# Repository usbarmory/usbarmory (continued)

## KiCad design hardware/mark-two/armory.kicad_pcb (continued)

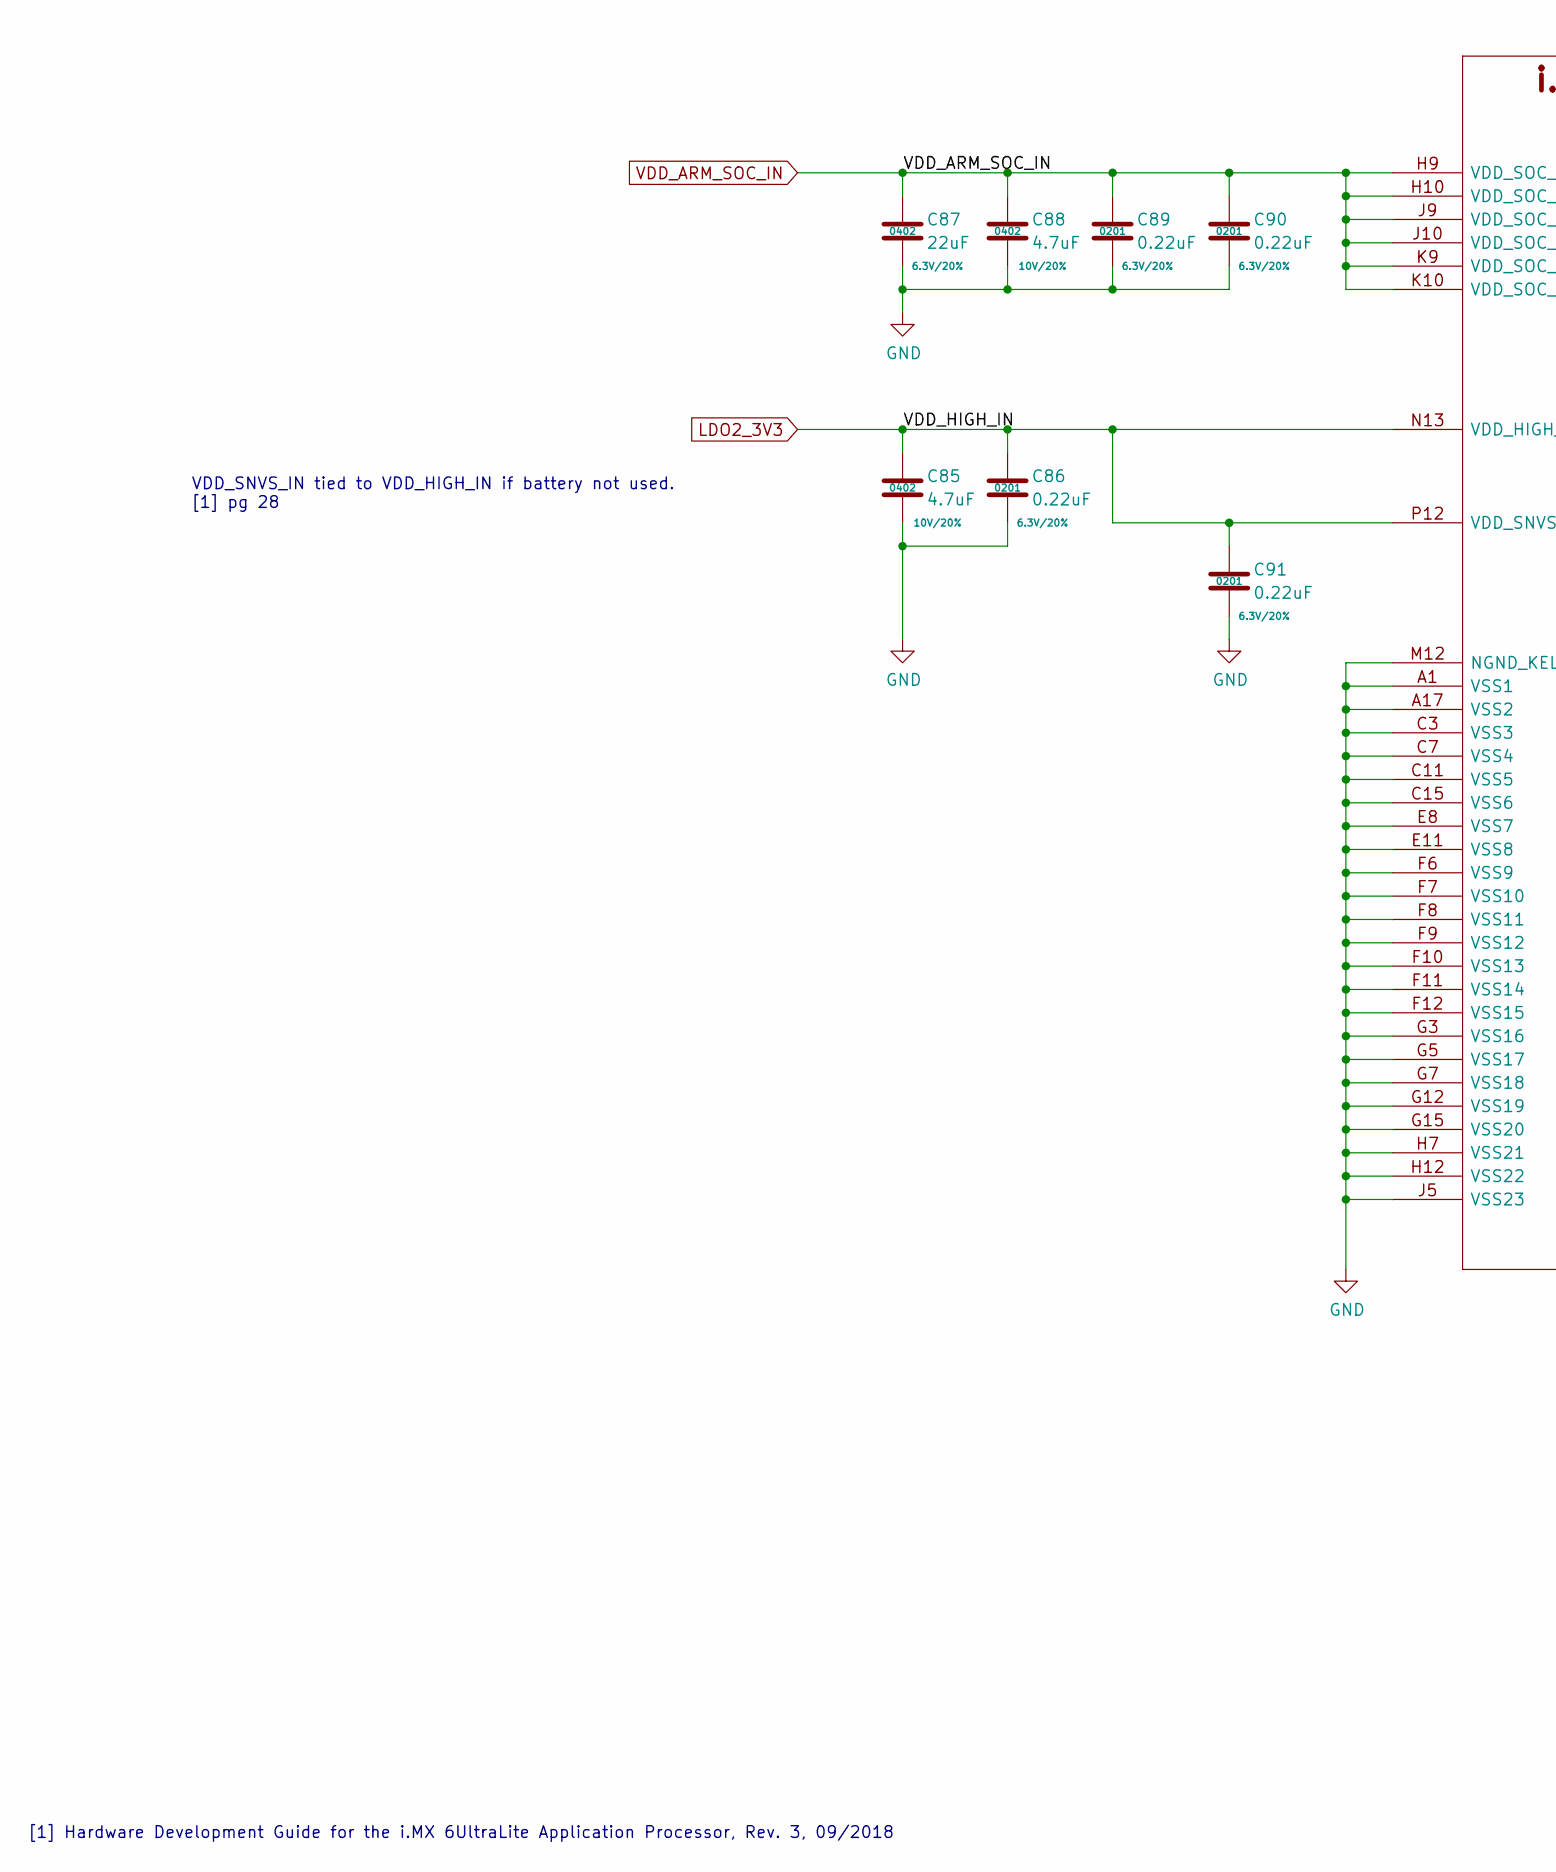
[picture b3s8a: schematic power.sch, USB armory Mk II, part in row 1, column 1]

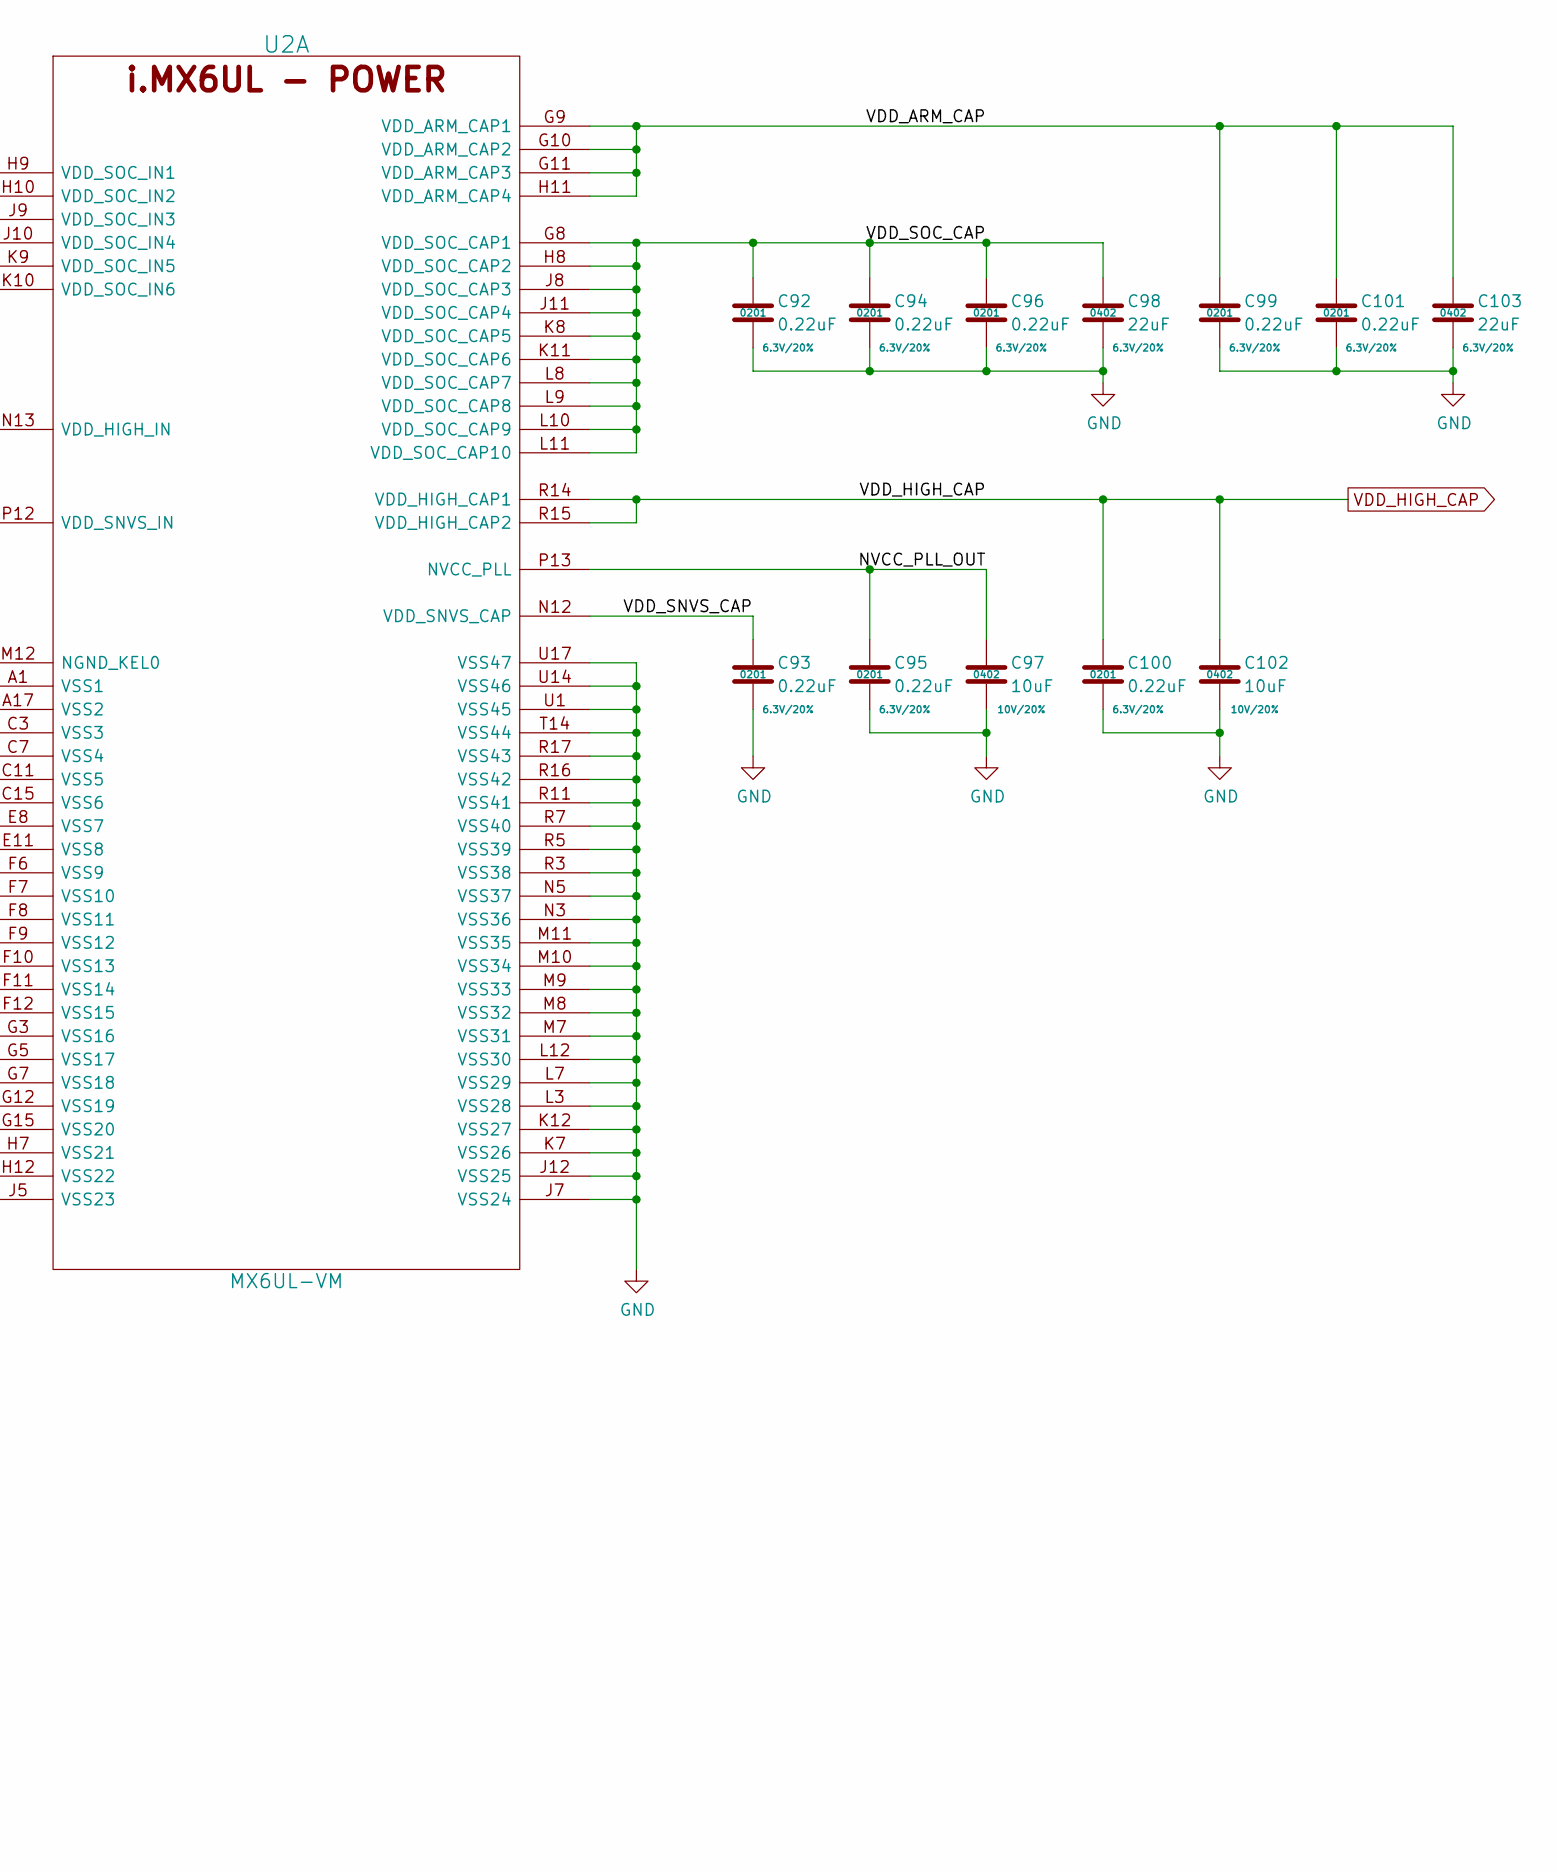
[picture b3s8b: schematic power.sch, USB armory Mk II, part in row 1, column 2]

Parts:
C85, C88: 4.7uF; SM0402; Rating 10V/20%; Mfg PN ZRB15XR61A475ME01D
C86, C89, C90, C91, C92, C93, C94, C95, C96, C99, C100, C101: 0.22uF; SM0201; Rating 6.3V/20%; Mfg PN GRM033R60J224ME15D
C87, C98, C103: 22uF; SM0402; Rating 6.3V/20%; Mfg PN CL05A226MQ5N6J8
C97, C102: 10uF; SM0402; Rating 10V/20%; Mfg PN CL05A106MP8NUB8
U2: MX6UL-VM; SOT1534-2; Mfg PN MCIMX6Z0DVM09AB

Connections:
/Power/NVCC_PLL_OUT: C95.1, C97.1, U2.P13 (NVCC_PLL)
/Power/VDD_ARM_CAP: C99.1, C101.1, C103.1, U2.G9 (VDD_ARM_CAP1), U2.G10 (VDD_ARM_CAP2), U2.G11 (VDD_ARM_CAP3), U2.H11 (VDD_ARM_CAP4)
/Power/VDD_SNVS_CAP: C93.1, U2.N12 (VDD_SNVS_CAP)
/Power/VDD_SOC_CAP: C92.1, C94.1, C96.1, C98.1, U2.G8 (VDD_SOC_CAP1), U2.H8 (VDD_SOC_CAP2), U2.J8 (VDD_SOC_CAP3), U2.J11 (VDD_SOC_CAP4), U2.K8 (VDD_SOC_CAP5), U2.K11 (VDD_SOC_CAP6), U2.L8 (VDD_SOC_CAP7), U2.L9 (VDD_SOC_CAP8), U2.L10 (VDD_SOC_CAP9), U2.L11 (VDD_SOC_CAP10)
GND: C85.2, C86.2, C87.2, C88.2, C89.2, C90.2, C91.2, C92.2, C93.2, C94.2, C95.2, C96.2, C97.2, C98.2, C99.2, C100.2, C101.2, C102.2, C103.2, U2.A1 (VSS1), U2.A17 (VSS2), U2.C3 (VSS3), U2.C7 (VSS4), U2.C11 (VSS5), U2.C15 (VSS6), U2.E8 (VSS7), U2.E11 (VSS8), U2.F6 (VSS9), U2.F7 (VSS10), U2.F8 (VSS11), U2.F9 (VSS12), U2.F10 (VSS13), U2.F11 (VSS14), U2.F12 (VSS15), U2.G3 (VSS16), U2.G5 (VSS17), U2.G7 (VSS18), U2.G12 (VSS19), U2.G15 (VSS20), U2.H7 (VSS21), U2.H12 (VSS22), U2.J5 (VSS23), U2.J7 (VSS24), U2.J12 (VSS25), U2.K7 (VSS26), U2.K12 (VSS27), U2.L3 (VSS28), U2.L7 (VSS29), U2.L12 (VSS30), U2.M7 (VSS31), U2.M8 (VSS32), U2.M9 (VSS33), U2.M10 (VSS34), U2.M11 (VSS35), U2.M12 (NGND_KEL0), U2.N3 (VSS36), U2.N5 (VSS37), U2.R3 (VSS38), U2.R5 (VSS39), U2.R7 (VSS40), U2.R11 (VSS41), U2.R16 (VSS42), U2.R17 (VSS43), U2.T14 (VSS44), U2.U1 (VSS45), U2.U14 (VSS46), U2.U17 (VSS47); also elsewhere on the board
LDO2_3V3: C85.1, C86.1, C91.1, U2.N13 (VDD_HIGH_IN), U2.P12 (VDD_SNVS_IN); also elsewhere on the board
VDD_ARM_SOC_IN: C87.1, C88.1, C89.1, C90.1, U2.H9 (VDD_SOC_IN1), U2.H10 (VDD_SOC_IN2), U2.J9 (VDD_SOC_IN3), U2.J10 (VDD_SOC_IN4), U2.K9 (VDD_SOC_IN5), U2.K10 (VDD_SOC_IN6); also elsewhere on the board
VDD_HIGH_CAP: C100.1, C102.1, U2.R14 (VDD_HIGH_CAP1), U2.R15 (VDD_HIGH_CAP2); also elsewhere on the board

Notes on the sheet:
[1] Hardware Development Guide for the i.MX 6UltraLite Application Processor, Rev. 3, 09/2018
VDD_SNVS_IN tied to VDD_HIGH_IN if battery not used. [1] pg 28

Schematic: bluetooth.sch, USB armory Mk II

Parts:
C104: 0.1uF; SM0201; Rating 10V/20%; Mfg PN GRM033R61A104ME15D
TP8, TP9: TestPoint; TP
U11: ANNA-B112; Mfg PN ANNA-B112-01B

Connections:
/Bluetooth/ANT_INT: U11.5 (ANT_INT), U11.6 (ANT)
/Bluetooth/ANT_PCB: U11.1 (ANT_PCB)
BT_RESET_B: U11.12 (~RESET); also elsewhere on the board
BT_SWDCLK: U11.39 (SWD_CLK); also elsewhere on the board
BT_SWDIO: U11.40 (SWD_IO); also elsewhere on the board
BT_SWITCH_1: U11.30 (GREEN/SWITCH_1); also elsewhere on the board
BT_SWITCH_2: U11.38 (SWITCH_2); also elsewhere on the board
BT_UART_CTS: U11.35 (UART_CTS); also elsewhere on the board
BT_UART_DSR: U11.26 (UART_DSR); also elsewhere on the board
BT_UART_DTR: U11.25 (UART_DTR); also elsewhere on the board
BT_UART_RTS: U11.34 (UART_RTS); also elsewhere on the board
BT_UART_RX: TP9.1, U11.19 (UART_TXD); also elsewhere on the board
BT_UART_TX: TP8.1, U11.20 (UART_RXD); also elsewhere on the board
DCDC_3V3: C104.1, U11.9 (VCC); also elsewhere on the board
GND: C104.2, U11.4 (GND), U11.7 (GND), U11.8 (GND), U11.10 (GND), U11.11 (GND), U11.17 (XL1), U11.18 (XL2), U11.32 (GND), U11.33 (GND), U11.41 (GND), U11.42 (GND), U11.43 (GND), U11.44 (GND), U11.46 (GND), U11.47 (GND), U11.48 (GND), U11.49 (GND), U11.50 (GND), U11.51 (GND), U11.52 (GND); also elsewhere on the board

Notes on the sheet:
When using internal oscillator XL1 and XL2 should be connected to ground ([1] pg 11).
Use internal antenna.
[1] ANNA-B112 - System Integration Manual (UBX-18009821-R07)
There is no strict requirement of adding bypass capacitance to the supply net close to the module. But depending on the layout of the supply net and other consumers on the same net, bypass capacitors might still be beneficial. [1] pg 40
NFC_1 and NFC_2: floating Not found any reference, but should be safe as they are also GPIO.
Integrated antenna module placed - in the corner of the PCB: ANT_PCB -> GND pattern ANT_GND_x -> NC - on the side of the PCB: ANT_PCB -> NC ANT_GND_x -> GND [1] pg 14
RESET_N: 13 kOhm internal pull-up. [2] pg 28
[2] ANNA-B112 - Data Sheet (UBX-18011707-R04)
It has been witnessed that the ANNA-B112 can be back-powered via UART pins. To turn completelly off the module all the interfaces pins should be kept low.

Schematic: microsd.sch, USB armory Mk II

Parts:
C37: 0.22uF; SM0201; Rating 6.3V/20%; Mfg PN GRM033R60J224ME15D
C105: 10uF; SM0402; Rating 10V/20%; Mfg PN CL05A106MP8NUB8
C106: 0.1uF; SM0201; Rating 10V/20%; Mfg PN GRM033R61A104ME15D
J1: microSD slot; MOLEX_503182-1852; Mfg PN 503182-1852
R54: 22R; SM0201; Rating 50mW/1%; Mfg PN CRCW020122R0JNED
R55, R56: 10K; SM0201; Rating 50mW/1%; Mfg PN CRCW020110K0JNED
U2: MX6UL-VM; SOT1534-2; Mfg PN MCIMX6Z0DVM09AB
U12: PUSB3TB6; SOT1358-1; Mfg PN PUSB3TB6AZ
U20, U21: TPD1E10B06; X1SON-2; Mfg PN TPD1E10B06DPYR

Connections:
/microSD/SD1_CLK: J1.5 (CLK), R54.1, U12.2 (CH2)
/microSD/SD1_CLK_R: R54.2, U2.C1 (SD1_CLK)
/microSD/SD1_CMD: J1.3 (CMD), R55.2, U2.C2 (SD1_CMD), U12.6 (CH5)
/microSD/SD1_DATA0: J1.7 (DAT0), R56.2, U2.B3 (SD1_DATA0), U12.7 (CH6)
/microSD/SD1_DATA1: J1.8 (DAT1), U2.B2 (SD1_DATA1), U12.1 (CH1)
/microSD/SD1_DATA2: J1.1 (DATA2), U2.B1 (SD1_DATA2), U12.5 (CH4)
/microSD/SD1_DATA3: J1.2 (CD/DAT3), U2.A2 (SD1_DATA3), U12.3 (CH3)
DCDC_3V3: C105.1, C106.1, J1.4 (VDD), U21.1; also elsewhere on the board
GND: C37.2, C105.2, C106.2, J1.6 (VSS), J1.DT (DETECT), J1.P1 (SHIELD), J1.P2 (SHIELD), J1.P3 (SHIELD), J1.P4 (SHIELD), J1.P5 (SHIELD), U12.4 (GND), U20.2, U21.2; also elsewhere on the board
SD1_CD_B: J1.SW (SWITCH), U20.1; also elsewhere on the board
SD_3V3_1V8: C37.1, R55.1, R56.1, U2.C4 (NVCC_SD1); also elsewhere on the board

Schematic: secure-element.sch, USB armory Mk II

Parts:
C5, C107: 0.1uF; SM0201; Rating 10V/20%; Mfg PN GRM033R61A104ME15D
R29: 10K; SM0201; Rating 50mW/1%; Mfg PN CRCW020110K0JNED
U4: SE050; SOT1969-1; Mfg PN SE050C1HQ1/Z01SCZ
U13: ATECC608B-DNP; UDFN-8; Mfg PN ATECC608B-MAHDA

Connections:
DCDC_3V3: C5.1, C107.1, R29.1, U4.12 (VIN), U13.8 (VCC); also elsewhere on the board
GND: C5.2, C107.2, U4.1 (ISO_14443_LB), U4.14 (ISO_7816_RST_N), U4.17 (ISO_14443_LA), U4.19 (VSS), U4.21 (Thermal), U13.4 (GND), U13.T (THERMAL); also elsewhere on the board
I2C1_SCL: U4.10 (I2C_SCL), U13.6 (SCL); also elsewhere on the board
I2C1_SDA: U4.9 (I2C_SDA), U13.5 (SDA); also elsewhere on the board
unnamed: U4.15 (VOUT), U4.18 (VCC)
SE050_ENA: R29.2, U4.11 (ENA); also elsewhere on the board

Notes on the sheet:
Optional, not mounted on retail units.

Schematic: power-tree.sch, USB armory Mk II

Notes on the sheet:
USB1_VBUS
USB2_VBUS
USB_VBUS
i.MX6ULZ
NVCC_ENET
VDD_SOC_IN
VDD_HIGH_IN
VDD_SNVS_IN
USB_OTG1_VBUS
VDDA_ADC_3P3
NVCC_GPIO
NVCC_CSI
NVCC_NAND
NVCC_SD1
NVCC_LCD
NVCC_UART
USB_OTG2_VBUS
NVCC_DRAM
NVCC_DRAM_2P5
Type-C port controller
VIN
FUSB303 - RCPT
TUSB320 - PLUG
Bluetooth module
u-blox ANNA-B112
Type-C debug switch
FSA1208
push-push slot
microSD
4GB/8GB/16GB eMMC
eMMC
DDR3L 512 MB / 1 GB
DDR
Microchip ATECC608A
Secure Element 1
Logic inverter
SN74LVC1G04
Type-C power switch
NX5P3090
A10

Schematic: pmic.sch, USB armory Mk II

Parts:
C1, C2, C3, C23: 4.7uF; SM0402; Rating 10V/20%; Mfg PN ZRB15XR61A475ME01D
C4, C8, C9, C10, C14, C15, C25: 1uF; SM0201; Rating 10V/20%; Mfg PN GRM033R61A105ME15D
C11, C12: 0.1uF; SM0201; Rating 10V/20%; Mfg PN GRM033R61A104ME15D
C13: 2.2uF; SM0402; Rating 25V/20%; Mfg PN GRM155R61E225ME15D
C16: 47uF; SM0603; Rating 6.3V/20%; Mfg PN GRM188R60J476ME15D
C17, C18, C20, C21, C22, C24, C26, C32: 10uF; SM0402; Rating 10V/20%; Mfg PN CL05A106MP8NUB8
C27: 0.47uF; SM0201; Rating 6.3V/20%; Mfg PN GRM033R60J474ME90D
L1, L2, L3: 1uH; SM0603; Rating 1.7A/20%/128mOhm; Mfg PN DFE18SAN1R0MG0L
R1, R2, R22: 100K; SM0201; Rating 50mW/1%; Mfg PN CRCW0201100KJNED
U1: MC34PF1510A6EP; SOT1369-4; Mfg PN MC34PF1510A6EP

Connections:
/PMIC/LICELL: C12.1, U1.31 (LICELL)
/PMIC/VCORE: C14.1, U1.24 (VCORE)
/PMIC/VDIG: C15.1, U1.23 (VDIG)
/PMIC/VSNVS_3V: C27.1, R1.1, R22.1, U1.30 (VSNVS)
/PMIC/VSYS: C1.1, C2.1, C3.1, C4.1, C8.1, C9.1, C16.1, R2.1, U1.11 (VLDO3IN), U1.14 (SW3IN), U1.17 (SW2IN), U1.20 (VLDO2IN), U1.26 (SW1IN), U1.28 (VLDO1IN), U1.35 (VSYS1), U1.36 (VSYS2)
DCDC_3V3: C11.1, C24.1, C26.1, L3.2, U1.4 (VDDIO), U1.15 (SW3FB); also elsewhere on the board
DDR_1V35: C10.1, C20.1, C22.1, L2.2, U1.16 (SW2FB), U1.22 (VINREFDDR); also elsewhere on the board
DDR_VREF: C25.1, U1.21 (VREFDDR); also elsewhere on the board
EMMC_1V8: C32.1, U1.29 (VLDO1); also elsewhere on the board
GND: C1.2, C2.2, C3.2, C4.2, C8.2, C9.2, C10.2, C11.2, C12.2, C13.2, C14.2, C15.2, C16.2, C17.2, C18.2, C20.2, C21.2, C22.2, C23.2, C24.2, C25.2, C26.2, C27.2, C32.2, U1.5 (VDDOTP), U1.7 (STANDBY), U1.32 (GND), U1.40 (GND), U1.41 (EP); also elsewhere on the board
I2C1_SCL: U1.3 (SCL); also elsewhere on the board
I2C1_SDA: U1.2 (SDA); also elsewhere on the board
LDO2_3V3: C21.1, U1.19 (VLDO2); also elsewhere on the board
unnamed: L1.1, U1.25 (SW1LX)
unnamed: L2.1, U1.18 (SW2LX)
unnamed: L3.1, U1.13 (SW3LX)
unnamed: R1.2, U1.6 (PWRON)
unnamed: R2.2, U1.8 (ONKEY)
PMIC_WDI: R22.2, U1.1 (WDI); also elsewhere on the board
SD_3V3_1V8: C23.1, U1.12 (VLDO3); also elsewhere on the board
VDD_ARM_SOC_IN: C17.1, C18.1, L1.2, U1.27 (SW1FB); also elsewhere on the board
VSYS_5V: C13.1, U1.37 (VIN); also elsewhere on the board

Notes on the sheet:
[1] PF1510 - Power management integrated circuit (PMIC) for low power application processors Rev 1.0, 23 May 2018
EPAD: Tie to the inner and external ground planes through vias to allow effective thermal dissipation. [1] pg 8
400 mA
300 mA
1 A
10 mA
Power rails
ULL/ULZ: NXP MC34PF1510A6EP UL: NXP MC32PF1510A3EP

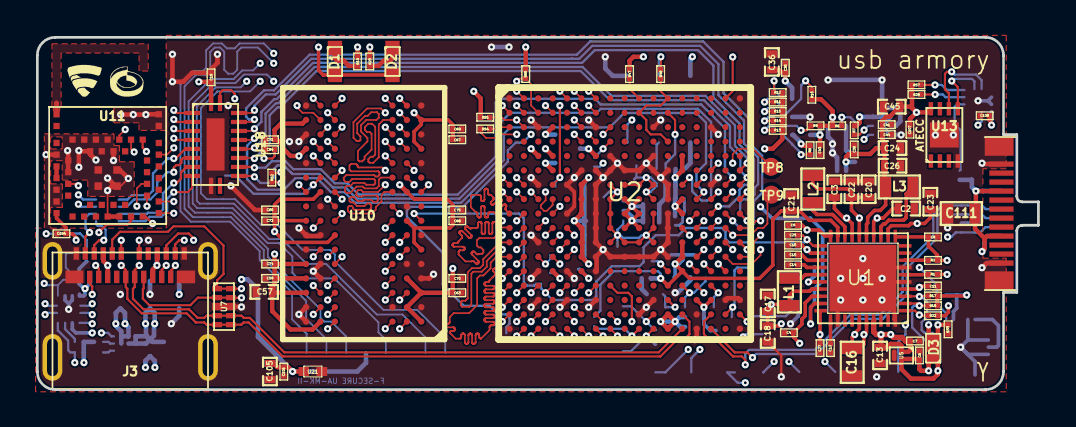
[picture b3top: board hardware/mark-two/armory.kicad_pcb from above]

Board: 6 copper layers, 55.6 x 19.6 mm, 195 parts (0 on the bottom side), 172 nets.

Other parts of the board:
FSC_LOGO_NO_TEXT_SMALL: G***; FSC_LOGO_NO_TEXT_SMALL
FSC_LOGO_NO_TEXT_SMALL#2: G***; FSC_LOGO_NO_TEXT_SMALL
Ref**: Val**; IP_LOGO_NO_TEXT_SMALL
Ref**#2: Val**; IP_LOGO_NO_TEXT_SMALL

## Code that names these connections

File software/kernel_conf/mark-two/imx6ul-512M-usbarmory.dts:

/*
 * USB armory Mk II device tree file
 * https://github.com/inversepath/usbarmory
 *
 * Copyright (c) The USB armory authors
 * Andrej Rosano <andrej@inversepath.com>
 *
 * This file is dual-licensed: you can use it either under the terms
 * of the GPL or the X11 license, at your option. Note that this dual
 * licensing only applies to this file, and not this project as a
 * whole.
 *
 *  a) This file is free software; you can redistribute it and/or
 *     modify it under the terms of the GNU General Public License as
 *     published by the Free Software Foundation; either version 2 of the
 *     License, or (at your option) any later version.
 *
 *     This file is distributed in the hope that it will be useful,
 *     but WITHOUT ANY WARRANTY; without even the implied warranty of
 *     MERCHANTABILITY or FITNESS FOR A PARTICULAR PURPOSE.  See the
 *     GNU General Public License for more details.
 *
 * Or, alternatively,
 *
 *  b) Permission is hereby granted, free of charge, to any person
 *     obtaining a copy of this software and associated documentation
 *     files (the "Software"), to deal in the Software without
 *     restriction, including without limitation the rights to use,
 *     copy, modify, merge, publish, distribute, sublicense, and/or
 *     sell copies of the Software, and to permit persons to whom the
 *     Software is furnished to do so, subject to the following
 *     conditions:
 *
 *     The above copyright notice and this permission notice shall be
 *     included in all copies or substantial portions of the Software.
 *
 *     THE SOFTWARE IS PROVIDED "AS IS", WITHOUT WARRANTY OF ANY KIND,
 *     EXPRESS OR IMPLIED, INCLUDING BUT NOT LIMITED TO THE WARRANTIES
 *     OF MERCHANTABILITY, FITNESS FOR A PARTICULAR PURPOSE AND
 *     NONINFRINGEMENT. IN NO EVENT SHALL THE AUTHORS OR COPYRIGHT
 *     HOLDERS BE LIABLE FOR ANY CLAIM, DAMAGES OR OTHER LIABILITY,
 *     WHETHER IN AN ACTION OF CONTRACT, TORT OR OTHERWISE, ARISING
 *     FROM, OUT OF OR IN CONNECTION WITH THE SOFTWARE OR THE USE OR
 *     OTHER DEALINGS IN THE SOFTWARE.
 */

/dts-v1/;

#include "imx6ul.dtsi"

/ {
	model = "F-Secure USB armory Mk II";
	compatible = "inversepath,imx6ul-usbarmory-mkII", "fsl,imx6ul";

	chosen {
		stdout-path = &uart2;
	};

	memory {
		device_type = "memory";
		reg = <0x80000000 0x20000000>;
	};

	leds {
		compatible = "gpio-leds";
		pinctrl-names = "default";
		pinctrl-0 = <&pinctrl_led>;

		led-white {
			label = "LED_WHITE";
			gpios = <&gpio4 21 GPIO_ACTIVE_LOW>;
			linux,default-trigger = "heartbeat";
		};

		led-blue {
			label = "LED_BLUE";
			gpios = <&gpio4 22 GPIO_ACTIVE_LOW>;
		};
	};

	regulators {
		compatible = "simple-bus";
		#address-cells = <1>;
		#size-cells = <0>;

		reg_sd1_vmmc: sd1_regulator {
			compatible = "regulator-fixed";
			regulator-name = "VSD_3V3";
			regulator-min-microvolt = <3300000>;
			regulator-max-microvolt = <3300000>;
		};
	};
};

&uart1 {
	pinctrl-names = "default";
	pinctrl-0 = <&pinctrl_bluetooth>;
	uart-has-rtscts;
	status = "okay";
};

&uart2 {
	pinctrl-names = "default";
	pinctrl-0 = <&pinctrl_uart2>;
	status = "okay";
};

&usdhc1 {
	pinctrl-names = "default";
	pinctrl-0 = <&pinctrl_usdhc1>;
	no-1-8-v;
	keep-power-in-suspend;
	wakeup-source;
	status = "okay";
};

&usdhc2 {
	pinctrl-names = "default";
	pinctrl-0 = <&pinctrl_usdhc2>;
	non-removable;
	status = "okay";
};

&i2c1 {
	pinctrl-0 = <&pinctrl_i2c1>;
	status = "okay";
};

&iomuxc {
	pinctrl_uart2: uart2grp {
		fsl,pins = <
			MX6UL_PAD_UART2_TX_DATA__UART2_DCE_TX	0x1b0b1
			MX6UL_PAD_UART2_RX_DATA__UART2_DCE_RX	0x1b0b1
		>;
	};

	pinctrl_bluetooth: uart1grp {
		fsl,pins = <
			MX6UL_PAD_UART1_TX_DATA__UART1_DCE_TX	0x1b0b0 /* BT_UART_TX  */
			MX6UL_PAD_UART1_RX_DATA__UART1_DCE_RX	0x1b0b0 /* BT_UART_RX  */
			MX6UL_PAD_UART1_CTS_B__UART1_DCE_CTS	0x1b0b0 /* BT_UART_CTS */
			MX6UL_PAD_GPIO1_IO07__UART1_DCE_RTS	0x130b0 /* BT_UART_RTS */
			MX6UL_PAD_UART3_TX_DATA__GPIO1_IO24	0x1f020 /* BT_UART_DSR */
			MX6UL_PAD_UART3_RX_DATA__GPIO1_IO25	0x10020 /* BT_UART_DTR */
			MX6UL_PAD_GPIO1_IO04__GPIO1_IO04	0x1f020 /* BT_SWDCLK   */
			MX6UL_PAD_GPIO1_IO06__GPIO1_IO06	0x1f020 /* BT_SWDIO    */
			MX6UL_PAD_GPIO1_IO09__GPIO1_IO09	0x1f020 /* BT_RESET    */
			MX6UL_PAD_UART3_RTS_B__GPIO1_IO27	0x1f020 /* BT_SWITCH_1 */
			MX6UL_PAD_UART3_CTS_B__GPIO1_IO26	0x1f020 /* BT_SWITCH_2 */
		>;
	};

	pinctrl_i2c1: i2c1grp {
		fsl,pins = <
			MX6UL_PAD_GPIO1_IO02__I2C1_SCL	0x4001b8b0
			MX6UL_PAD_GPIO1_IO03__I2C1_SDA	0x4001b8b0
		>;
	};

	pinctrl_led: ledgrp {
		fsl,pins = <
			MX6UL_PAD_CSI_DATA00__GPIO4_IO21	0x1f020
			MX6UL_PAD_CSI_DATA01__GPIO4_IO22	0x1f020
		>;
	};

	pinctrl_usdhc1: usdhc1grp {
		fsl,pins = <
			MX6UL_PAD_SD1_CMD__USDHC1_CMD		0x1f019
			MX6UL_PAD_SD1_CLK__USDHC1_CLK		0x1f019
			MX6UL_PAD_SD1_DATA0__USDHC1_DATA0	0x1f019
			MX6UL_PAD_SD1_DATA1__USDHC1_DATA1	0x1f019
			MX6UL_PAD_SD1_DATA2__USDHC1_DATA2	0x1f019
			MX6UL_PAD_SD1_DATA3__USDHC1_DATA3	0x1f019
		>;
	};

	pinctrl_usdhc2: usdhc2grp {
		fsl,pins = <
			MX6UL_PAD_NAND_RE_B__USDHC2_CLK		0x10071
			MX6UL_PAD_NAND_WE_B__USDHC2_CMD		0x17059
			MX6UL_PAD_NAND_DATA00__USDHC2_DATA0	0x17059
			MX6UL_PAD_NAND_DATA01__USDHC2_DATA1	0x17059
			MX6UL_PAD_NAND_DATA02__USDHC2_DATA2	0x17059
			MX6UL_PAD_NAND_DATA03__USDHC2_DATA3	0x17059
			MX6UL_PAD_NAND_DATA04__USDHC2_DATA4	0x17059
			MX6UL_PAD_NAND_DATA05__USDHC2_DATA5	0x17059
			MX6UL_PAD_NAND_DATA06__USDHC2_DATA6	0x17059
			MX6UL_PAD_NAND_DATA07__USDHC2_DATA7	0x17059
		>;
	};
};

/ {
	soc {
		caam_sm: caam-sm@00100000 {
			 compatible = "fsl,imx7d-caam-sm", "fsl,imx6q-caam-sm";
			 reg = <0x00100000 0x3fff>;
		};

		irq_sec_vio: caam_secvio {
			     compatible = "fsl,imx7d-caam-secvio", "fsl,imx6q-caam-secvio";
			     interrupts = <GIC_SPI 20 IRQ_TYPE_LEVEL_HIGH>;
		};
	};

	caam_keyblob: caam-keyblob {
		compatible = "fsl,sec-v4.0-keyblob";
		status = "okay";
	};
};

&usbotg1 {
	dr_mode = "peripheral";
	disable-over-current;
	tpl-support;
	status = "okay";
};

&usbotg2 {
	dr_mode = "host";
	disable-over-current;
	tpl-support;
	status = "okay";
};

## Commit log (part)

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2016-06-08 Remove old U-Boot patches
2016-06-09 bump buildroot INTERLOCK revision
2016-06-20 Add patch for disabling U-Boot CLI
2016-06-21 devicetree: explicitly set IOMUX values
    Do not relay on bootloader values (e.g. using 0x80000000 settings).
2016-06-21 devicetree: remove vpu node
    VPU is already enabled in imx53.dtsi.
2016-06-23 out of an abundance of caution (as at that time haveged already took care of the pool) ensure that there is enough entropy for luksFormat command
2016-06-28 Update kernel config
    Add stack protector and DMA contiguous access support.
2016-06-29 add SCCv2 device
2016-07-01 add mxc-scc2 driver in buildroot image and fix invalid date reset format
2016-07-03 tidying
2016-07-27 Update kernel config
    Use regular stack protection as gcc included in some main Linux
    distributions does not support -fstack-protector-strong flag yet.
2016-08-31 Add config for Linux 4.7
2016-09-16 isolate networking and INTERLOCK overlays for better modularity and bump revisions
2016-09-19 buildroot overlays/profiles re-org
2016-10-12 csftool: add support for Serial download mode when using DCD
    When DCD is used, Serial downloader will move DCD into ocram and clear
    the DCD pointer in IVT - before signature verification.
    To sign the image properly we need to:
    - clear the DCD pointer in IVT and calculate signature on this modified image
    - make a signature for DCD copy in ocram (usually from 0x910000)
2016-10-12 typo fix
2016-10-12 disable NTP server to favor manual configuration by user
2016-10-12 set static CDC Ethernet MAC address
2016-10-12 buildroot fixes: ensure LED is turned on last at shutdown, tidy overlay structure
2016-10-14 Add config for Linux 4.8
2016-10-21 bugfixes for qubes-gpg-split/gpg-server execution
2016-10-31 bump buildroot INTERLOCK and kernel revision
2016-11-08 improve readibility
2016-11-08 Fix typo
2016-11-09 check for dropbearkey dependency and note it in documentation
2016-11-10 fail on any post build error
2016-11-14 style consistency fixes
2016-11-15 lock alias now actually locks the partition
2016-11-15 add missing sudo
2016-11-16 bump kernel
2016-11-16 set default LED timeout if not specified
2016-11-17 Updated kernel configuration.
    Add support for EXT4 extended attributes to allow setcap, enable /proc/config.gz by default.
2016-11-22 replace diagram
2016-12-13 Clean old kernel configs
2016-12-13 Update devicetree files
    Add dts files for kernel 4.9. Move old dts files to dts-4.8 directory.
2016-12-15 restore scc2 dts entry in separate file
2017-01-14 PaX/Grsecurity 4.8 for USBArmory
2017-01-14 More exploit mitigation on Linux v4.9
2017-02-15 PaX/Grsecurity 4.9 for USBArmory:
    PaX/Grsecurity 4.9 with BBR enabled for the case of tor-router usage.
2017-02-15 PaX/Grsecurity 4.9 for USBArmory: (#38)
    PaX/Grsecurity 4.9 with BBR enabled for the case of tor-router usage.
2017-03-07 bump buildroot, INTERLOCK and mxc-scc2 revisions
2017-03-15 cryptsetup aes-xts-plain64 is broken under 4.10 kernel when sahara is enabled, make it a module for blacklisting when required
2017-05-24 bump buildroot and kernel revision
2017-06-05 add preliminary HAB security advisory
2017-07-19 CVE-2017-7932 PoC and advisory update
2017-07-27 added link to i.MX Community post that lists affected P/Ns
2017-08-07 bump INTERLOCK version
2017-11-17 update kernel conf
2018-01-08 update buildroot environment
2018-01-09 adjust mkfs.ext4 path due to change in newer buildroot
2018-01-15 Enable kernel namespaces
2018-02-13 Fix ext2load dependancy in secure boot patches
2018-02-14 bump initial system date
2018-02-15 Enable hab_status in secure boot patches
2018-02-20 Add linux kernel 4.14 config
2018-02-26 Fix disable CLI patch
    2018.01 U-Boot requires CONFIG_USE_BOOTARGS
2018-02-28 bump buildroot kernel, U-Boot and INTERLOCK versions
2018-05-08 Fix ext2load command not available error
2018-07-10 copyright change
2018-10-18 tidying
    Remove configurations for unmantained kernel versions
2018-11-01 Add devicetree with CAAM for i.MX6UL PICO board
2018-11-01 Add buildroot caam-keyblob package
2018-11-01 Bump U-Boot in INTERLOCK buildroot for i.MX6UL PICO
2018-11-01 Tyding
2018-11-01 Add i.MX6UL PICO secure boot support
2018-11-02 U-Boot security advisory (CVE-2018-18440, CVE-2018-18439)
2018-11-02 Remove unnecessary U-Boot environment variables
2018-11-02 imx6ul-pico: add patch for disabling U-Boot CLI
2018-11-27 adjust buildroot profiles to use intree dts
2018-12-04 fix documentation - dtb destination file
2018-12-18 bump caam-keyblob version
2019-02-01 maintain original dtb name to respect usbarmory.its path
2019-02-01 Update buildroot release and kernel version
2019-03-19 Fix i2c, spi and gpio devicetree
    iomux pinctrl configuration should be placed in module structure instead
    of the 'iomux' one. This behaviour seems to have changed in recent
    kernels.
2019-03-20 Fix I2C, GPIO and SPI devicetree files
    Remove container node from iomuxc nodes.
2019-03-28 bump buildroot and kernel versions for INTERLOCK profile
2019-04-01 move mark-one specific design files in own directory
2019-04-03 Set SION bit for i2c pads
2019-04-10 i.MX6UL* bootrom dump utility
2019-05-06 Update 4.14 kernel config
2019-05-06 enable local system does not support BPF/cgroup based firewalling
2019-05-08 adjust links
2019-05-08 add image links
2019-06-05 USB armory Mk II alpha buildroot profile
2019-06-06 adjust LED path
2019-06-06 Update usbarmory mark-two devicetree
    Add support for bluetooth GPIOs (switches, reset, etc.)
2019-06-06 Fix DDR calibration values
2019-06-07 Add FUSB303 reset in U-Boot
2019-06-10 Disable over current detection for i.MX6UL
2019-06-10 i.MX6UL and i.MX6ULL device tree files update
    - enable hardware flow control on bluetooth uart
    - set plug USB port to peripheral mode
    - tidying
2019-06-12 preliminary mark-two 4.19 kernel configuration
2019-06-12 move mark-two buildroot configuration to kernel 4.19
2019-06-12 remove imx6ul pico configuration and replace it with mark-two specific one
2019-06-14 set i.MX6ULL as default DTS
2019-06-14 USB armory mark-two debug accessory
2019-06-20 comment FUSB303 i2c enable lines in u-boot patches
2019-06-20 adjust path
2019-06-20 use capabilities over tmpfs
2019-06-20 remove development ssh access
2019-06-21 enable CONFIG_IMX2_WDT to allow reboot
2019-06-24 force HAB_ENG_SW due to i.MX6ULL/i.MX6ULZ ERR010449
2019-06-27 Do not reloacate fdt initrd images
    Required to boot Linux on boards with 1GB RAM.
2019-06-27 Add U-Boot patches for boards with 1GB RAM
2019-07-01 disable CAAM on i.MX6ULL/i.MX6ULZ
2019-07-01 restore ENABLE on receptacle port
2019-07-01 bump kernel version
2019-07-01 restore USB PHY settings
2019-07-10 Fix U-Boot environment offset
    Move environment offset to 1MB to keep enough space for
    U-Boot image.
2019-07-12 first attempt at Travis CI for buildroot environment
2019-07-12 set variables as global
2019-07-12 reduce log size
2019-07-12 wait for make command
2019-07-12 remove travis integration due to time limit
2019-07-15 Add U-Boot 2017.04 patch for upstream
2019-07-22 set uSD as non-removable to work around U-Boot issue with CD
2019-07-22 specify i.MX6ULZ specific behaviour
2019-07-23 bump buildroot kernel versions
2019-07-23 Fix patch for upstream to support disabled console
    A revert of commit 80a48dd47e3bf3ede676fae5a630cb6c80de3e69
    is required to make the build successful, otherwise the following
    error is returned at the final linking stage:
    ...
    LDS u-boot.lds
    LD u-boot
2019-07-25 U-Boot advisory update
2019-07-31 bump buildroot kernel versions and apply updated mark-two u-boot patches
2019-07-31 Fix U-boot patch
    Add missing spaces in defconfig file.
2019-08-02 Fix IOMUX configuration for UART1 in U-Boot patch
2019-08-05 Fix U-Boot patch related to 1GB DDR support
2019-08-07 bump kernel versions
2019-08-07 Fix typos
2019-08-21 note orientation requirement
2019-08-26 clarify licensing
2019-09-09 Set dr_mode for plug port to peripheral
2019-09-25 Fix U-Boot mmc initialization
    Move iomux initialization for eMMC and microSD back to
    board file as the initialization via dts file appears buggy.
2019-09-30 bumped latest mxc-scc2 changeset
2019-11-07 USB armory Mk II project files + tidying
2019-11-08 add USB armory Mk II information in HAB advisory
2020-01-13 rename organization
2020-02-24 point to github page
2020-03-06 highlight default credentials
2020-03-18 add config for linux 5.4
2020-03-18 u-boot: specify boot configuration
    Mitigates CVE-2020-10648
    https://labs.f-secure.com/advisories/das-u-boot-verified-boot-bypass
2020-03-25 Fix argc argument to include USBARMORY_FIT_SIZE
    The argc argument in do_ext2load function is incorrect,
    preventing the use of USBARMORY_FIT_SIZE parameter.
2020-03-26 add serial console example for base Debian image
2020-04-02 Limit distro_bootcmd to scan a single boot device
    Regardless of the boot device, the distro_bootcmd scans both,
    microSD and eMMC, for boot scripts presence.
    A situation can arise where the U-Boot is booted from one device,
    and the Linux boot scripts are read from the other, preventing
    a complete boot from the expected device.
2020-04-02 Remove not required device tree blocks
2020-04-10 Add Mk II JTAG schematics
2020-04-24 Add DCD file for i.MX6ULZ 512MB
2020-05-04 Fix cpufreq support for imx6ulz
    https://groups.google.com/forum/#!topic/usbarmory/p4I0e22rKYw
2020-05-18 Updated DTS to use operating-points-v2 for imx6ulz
2020-06-03 remove U-Boot UMS patches, now replaced by armory-ums
2020-06-11 replace U-Boot UMS with armory-ums in buildroot installation procedure
2020-06-11 usbarmory linux: add CONFIG_SECURITY_APPARMOR
2020-06-12 u-boot: bump patches to 2020.04
2020-06-15 Fix verification boot for U-Boot 2020.04
    Remove the 'signature' devicetree block form imx6ul-usbarmory.dts
    as it goes in conflict with the one specified in usbarmory.its.
2020-06-15 Fix paths
2020-06-25 add errata note
2020-07-04 add errata comment
2020-07-24 allow crypto engine override
2020-09-17 Fix IOMUX configuration for LEDs
2020-10-20 bump u-boot patch to v2020.10
2020-12-11 update step file
2021-01-07 Add netfilter xt modules
2021-03-10 u-boot: enable TEE support
2021-03-10 u-boot: bump to v2021.01
2021-03-10 kernel: add linux config 5.10
    - add TEE support
    - align dts file for 5.10 kernel version
2021-03-10 align imx6ul devicetree to kernel 5.10
2021-03-15 add link to habtool
2021-05-07 linux: update config for 5.10.34
2021-05-14 buildroot update
2021-06-14 add USB armory Mk II rev. γ STEP file
2021-07-22 u-boot: bump to v2021.07
2021-07-30 Add HS200 MMC mode
    On gamma use HS200 mode on eMMC:
    mmc1: new HS200 MMC card at address 0001
    On beta revisions will fallback to default DDR MMC mode:
    mmc1: mmc_select_hs200 failed, error -74
    mmc1: new DDR MMC card at address 0001
2021-08-04 Fix debug accessory documentation
2021-09-20 links update
2021-09-30 buildroot profiles are no longer mantained
2021-11-12 Enable cpu idle
2021-11-12 Align U-Boot config to v2021.10
2021-11-22 Compile RNGB driver as module
2021-11-23 Revert "Compile RNGB driver as module"
    This reverts commit 99c710d7c7e7e14902887094457c5fd03dc011d2.
2021-11-23 Add dts node for optee driver
2022-03-09 Add config for linux 5.15
2022-03-10 mark-one: add config for linux 5.15
2022-03-23 Add kernel defconfig for mark-one and mark-two
2022-03-28 Align to U-Boot v2022.01
2022-03-28 Fix verified boot
    Based on:
    https://github.com/sergioag/usbarmory_u-boot/commit/a325c085feacb1468811dcc2a8a9d5b4fde8744d
2022-03-31 fix mark-one USB
2022-05-09 Align to U-Boot v2022.04
2022-06-28 bump u-boot patch to v2022.04
2022-07-19 Fix boot in non-secure mode
2022-07-20 Align to U-Boot v2022.07
2022-11-14 Align to U-Boot 2022.10
2022-11-23 imc6ul: use 1GB ram
2023-01-12 linux: enable binfmt_misc
2023-03-15 Align to U-Boot 2023.01
2023-04-14 add dts
2023-05-02 Add imx6ulz 1G non secure devicetree
2023-06-20 Align to U-Boot 2023.04
2023-07-20 Align to U-Boot v2023.07
2023-07-20 Fix for mark-one u-boot
2023-10-02 add PoE silkscreen
2023-11-10 Fix comments
2024-01-26 bump u-boot config to 2024.01
2024-04-04 bump u-boot config to 2024.04
2024-04-19 add USB armory Mk II LAN configs
2024-07-02 bump u-boot config to 2024.07
2024-10-29 bump u-boot patch to 2024.10
2025-04-10 bump u-boot- patch to 2025.04
2025-04-28 update emails
2025-08-28 license/copyright update
